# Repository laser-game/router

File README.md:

# Router
Devices for route wireless communication between the control computer and laser game devices.

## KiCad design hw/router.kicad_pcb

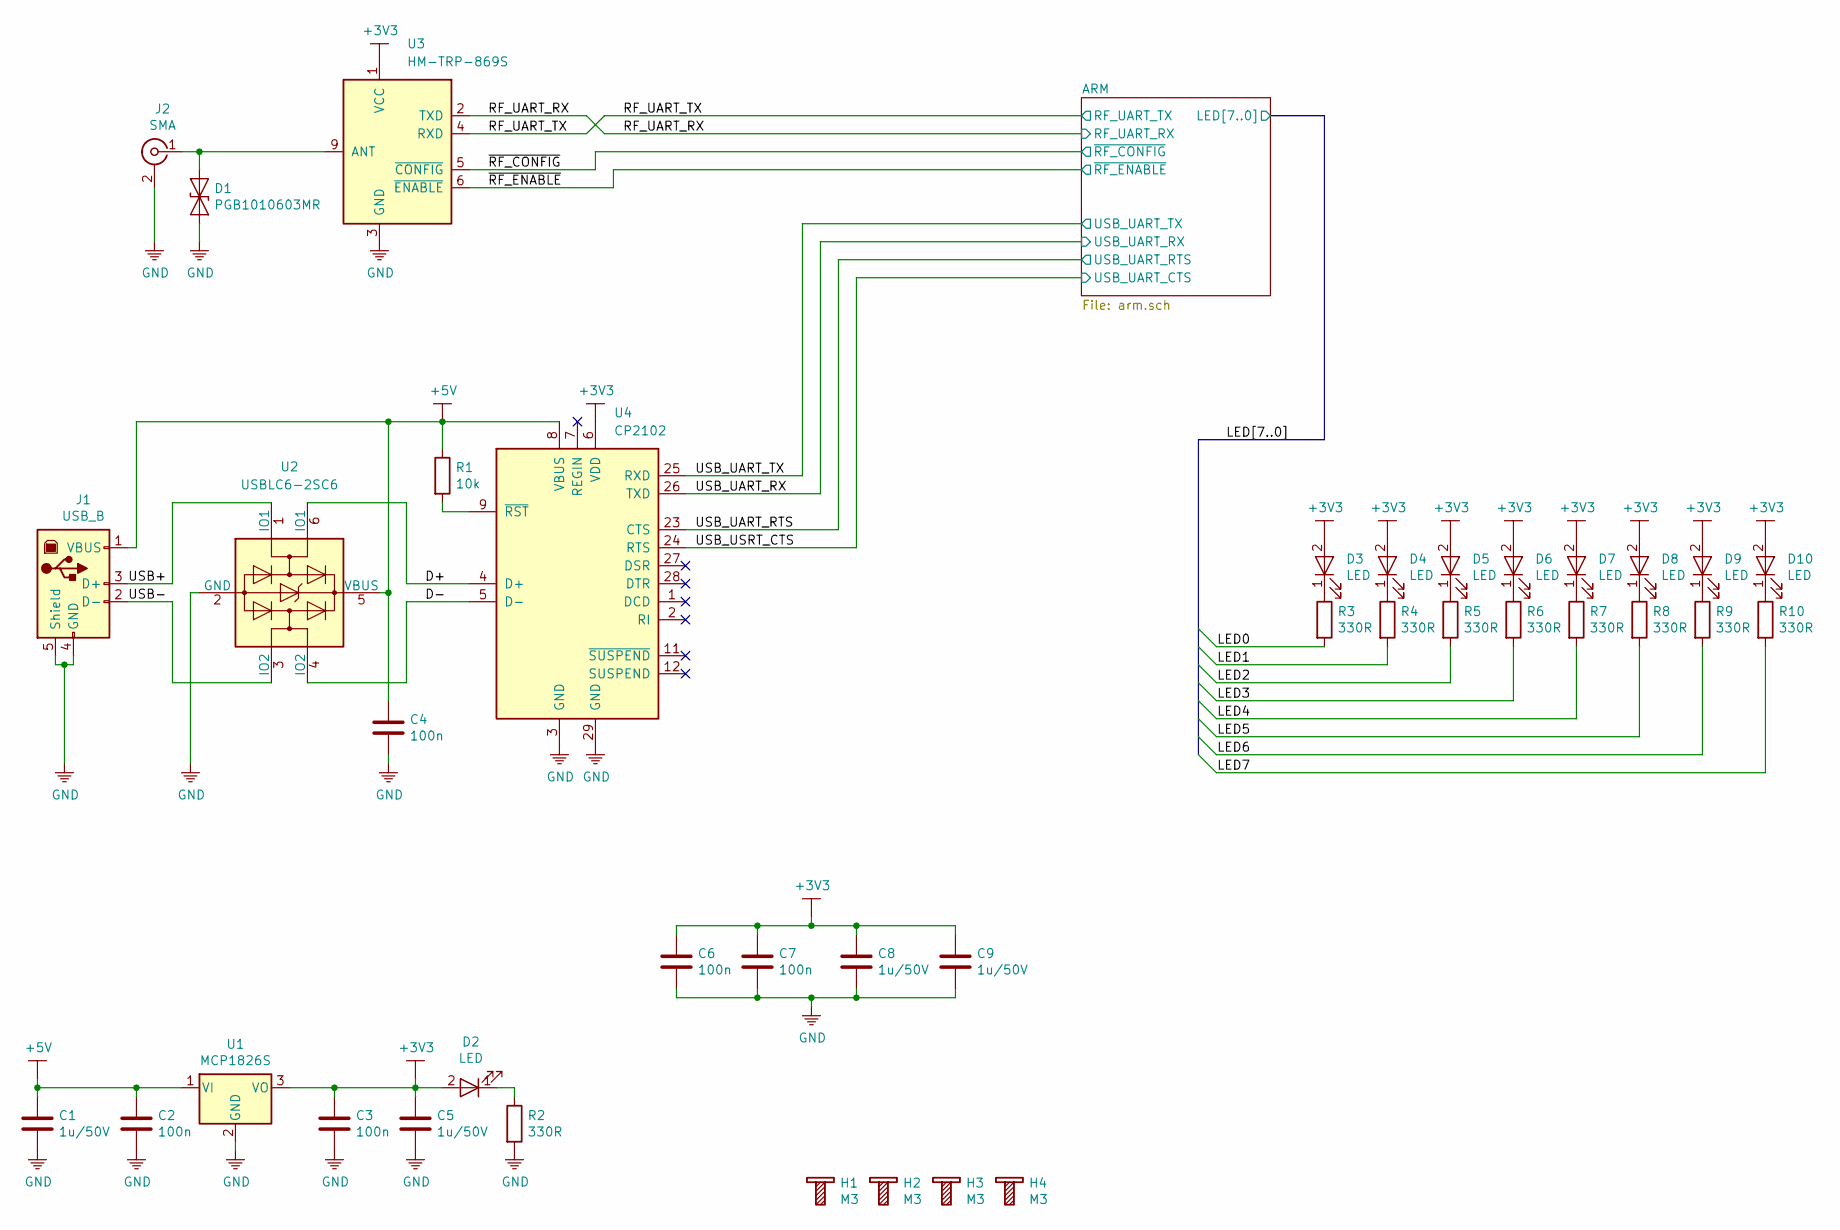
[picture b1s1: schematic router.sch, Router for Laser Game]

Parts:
C1, C5, C8, C9: 1u/50V; C_0805_2012Metric
C2, C3, C4, C6, C7: 100n; C_0805_2012Metric
D1: PGB1010603MR; D_0603_1608Metric
D2, D3, D4, D5, D6, D7, D8, D9, D10: LED; LED_0805_2012Metric
H1, H2, H3, H4: M3; Bolt_M3
J1: USB_B; USB_B_TE_5787834_Vertical
J2: SMA; SMA_Jack_Vertical
R1: 10k; R_0805_2012Metric
R2, R3, R4, R5, R6, R7, R8, R9, R10: 330R; R_0805_2012Metric
U1: MCP1826S; SOT-223-3_TabPin2
U2: USBLC6-2SC6; SOT-23-6
U3: HM-TRP-869S; HM-TRP-SMD
U4: CP2102; QFN-28-1EP_5x5mm_P0.5mm_EP3.35x3.35mm

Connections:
+3V3: C3.1, C5.1, C6.1, C7.1, C8.1, C9.1, D2.2 (A), D3.2 (A), D4.2 (A), D5.2 (A), D6.2 (A), D7.2 (A), D8.2 (A), D9.2 (A), D10.2 (A), U1.3 (VO), U3.1 (VCC), U4.6 (VDD); also elsewhere on the board
+5V: C1.1, C2.1, C4.1, J1.1 (VBUS), R1.1, U1.1 (VI), U2.5 (VBUS), U4.8 (VBUS)
/D+: U2.6 (IO1), U4.4 (D+)
/D-: U2.4 (IO2), U4.5 (D-)
/LED0: R3.2; also elsewhere on the board
/LED1: R4.2; also elsewhere on the board
/LED2: R5.2; also elsewhere on the board
/LED3: R6.2; also elsewhere on the board
/LED4: R7.2; also elsewhere on the board
/LED5: R8.2; also elsewhere on the board
/LED6: R9.2; also elsewhere on the board
/LED7: R10.2; also elsewhere on the board
/RF_UART_RX: U3.2 (TXD); also elsewhere on the board
/RF_UART_TX: U3.4 (RXD); also elsewhere on the board
/USB+: J1.3 (D+), U2.1 (IO1)
/USB-: J1.2 (D-), U2.3 (IO2)
/USB_UART_RTS: U4.23 (CTS); also elsewhere on the board
/USB_UART_RX: U4.26 (TXD); also elsewhere on the board
/USB_UART_TX: U4.25 (RXD); also elsewhere on the board
/USB_USRT_CTS: U4.24 (RTS); also elsewhere on the board
/~RF_CONFIG: U3.5 (~CONFIG); also elsewhere on the board
/~RF_ENABLE: U3.6 (~ENABLE); also elsewhere on the board
GND: C1.2, C2.2, C3.2, C4.2, C5.2, C6.2, C7.2, C8.2, C9.2, D1.2 (A2), J1.4 (GND), J1.5 (Shield), J2.2 (Ext), R2.2, U1.2 (GND), U2.2 (GND), U3.3 (GND), U3.8 (GND), U4.3 (GND), U4.29 (GND); also elsewhere on the board
unnamed: D1.1 (A1), J2.1 (In), U3.9 (ANT)
unnamed: D2.1 (K), R2.1
unnamed: D3.1 (K), R3.1
unnamed: D4.1 (K), R4.1
unnamed: D5.1 (K), R5.1
unnamed: D6.1 (K), R6.1
unnamed: D7.1 (K), R7.1
unnamed: D8.1 (K), R8.1
unnamed: D9.1 (K), R9.1
unnamed: D10.1 (K), R10.1
unnamed: R1.2, U4.9 (~RST)

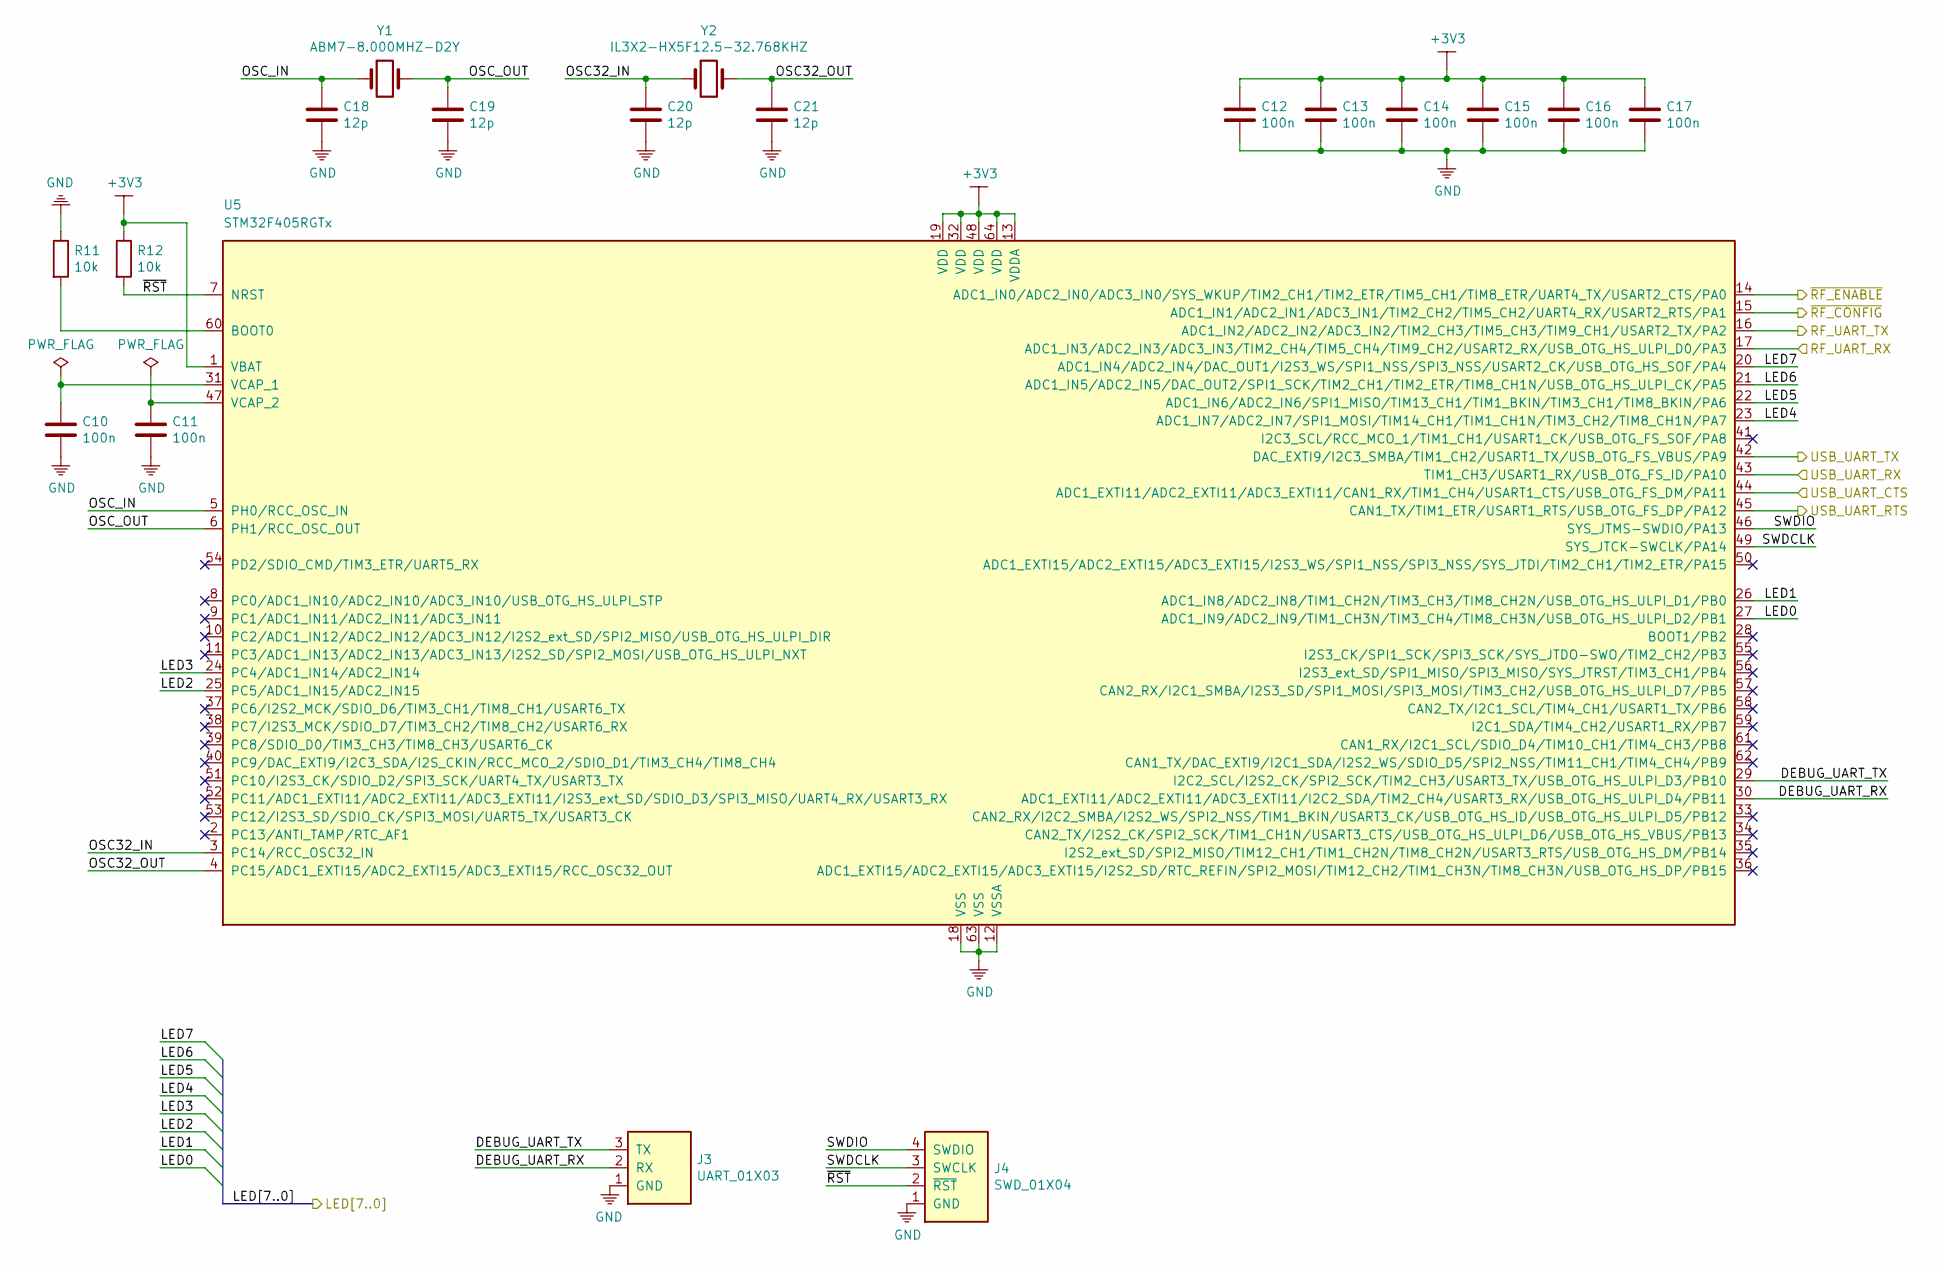
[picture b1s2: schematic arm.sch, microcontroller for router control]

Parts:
C10, C11, C12, C13, C14, C15, C16, C17: 100n; C_0805_2012Metric
C18, C19, C20, C21: 12p; C_0805_2012Metric
J3: UART_01X03; PinHeader_1x03_P2.54mm_Vertical
J4: SWD_01X04; PinHeader_1x04_P2.54mm_Vertical
R11, R12: 10k; R_0805_2012Metric
U5: STM32F405RGTx; TQFP-64_10x10mm_P0.5mm
Y1: ABM7-8.000MHZ-D2Y; Crystal_SMD_2012-2Pin_2.0x1.2mm_HandSoldering
Y2: IL3X2-HX5F12.5-32.768KHZ; Crystal_SMD_2012-2Pin_2.0x1.2mm_HandSoldering

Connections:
+3V3: C12.1, C13.1, C14.1, C15.1, C16.1, C17.1, R12.1, U5.1 (VBAT), U5.13 (VDDA), U5.19 (VDD), U5.32 (VDD), U5.48 (VDD), U5.64 (VDD); also elsewhere on the board
/ARM/DEBUG_UART_RX: J3.2 (RX), U5.30 (ADC1_EXTI11/ADC2_EXTI11/ADC3_EXTI11/I2C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)
/ARM/DEBUG_UART_TX: J3.3 (TX), U5.29 (I2C2_SCL/I2S2_CK/SPI2_SCK/TIM2_CH3/USAR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)
/ARM/OSC32_IN: C20.1, U5.3 (PC14/RCC_OSC32_IN), Y2.1
/ARM/OSC32_OUT: C21.1, U5.4 (PC15/ADC1_EXTI15/ADC2_EXTI15/ADC3_EXTI1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), Y2.2
/ARM/OSC_IN: C18.1, U5.5 (PH0/RCC_OSC_IN), Y1.1
/ARM/OSC_OUT: C19.1, U5.6 (PH1/RCC_OSC_OUT), Y1.2
/ARM/SWDCLK: J4.3 (SWCLK), U5.49 (SYS_JTCK-SWCLK/PA14)
/ARM/SWDIO: J4.4 (SWDIO), U5.46 (SYS_JTMS-SWDIO/PA13)
/ARM/~RST: J4.2 (~RST), R12.2, U5.7 (NRST)
/LED0: U5.27 (ADC1_IN9/ADC2_IN9/TIM1_CH3N/TIM3_CH4/TI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); also elsewhere on the board
/LED1: U5.26 (ADC1_IN8/ADC2_IN8/TIM1_CH2N/TIM3_CH3/TI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); also elsewhere on the board
/LED2: U5.25 (PC5/ADC1_IN15/ADC2_IN15); also elsewhere on the board
/LED3: U5.24 (PC4/ADC1_IN14/ADC2_IN14); also elsewhere on the board
/LED4: U5.23 (ADC1_IN7/ADC2_IN7/SPI1_MOSI/TIM14_CH1/T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); also elsewhere on the board
/LED5: U5.22 (ADC1_IN6/ADC2_IN6/SPI1_MISO/TIM13_CH1/T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); also elsewhere on the board
/LED6: U5.21 (ADC1_IN5/ADC2_IN5/DAC_OUT2/SPI1_SCK/TIM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); also elsewhere on the board
/LED7: U5.20 (ADC1_IN4/ADC2_IN4/DAC_OUT1/I2S3_WS/SPI1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); also elsewhere on the board
/RF_UART_RX: U5.17 (ADC1_IN3/ADC2_IN3/ADC3_IN3/TIM2_CH4/TIM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); also elsewhere on the board
/RF_UART_TX: U5.16 (ADC1_IN2/ADC2_IN2/ADC3_IN2/TIM2_CH3/TIM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); also elsewhere on the board
/USB_UART_RTS: U5.45 (CAN1_TX/TIM1_ETR/USART1_RTS/USB_OTG_FS_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); also elsewhere on the board
/USB_UART_RX: U5.43 (TIM1_CH3/USART1_RX/USB_OTG_FS_ID/PA10); also elsewhere on the board
/USB_UART_TX: U5.42 (DAC_EXTI9/I2C3_SMBA/TIM1_CH2/USART1_TX/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); also elsewhere on the board
/USB_USRT_CTS: U5.44 (ADC1_EXTI11/ADC2_EXTI11/ADC3_EXTI11/CAN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); also elsewhere on the board
/~RF_CONFIG: U5.15 (ADC1_IN1/ADC2_IN1/ADC3_IN1/TIM2_CH2/TIM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); also elsewhere on the board
/~RF_ENABLE: U5.14 (ADC1_IN0/ADC2_IN0/ADC3_IN0/SYS_WKUP/TIM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); also elsewhere on the board
GND: C10.2, C11.2, C12.2, C13.2, C14.2, C15.2, C16.2, C17.2, C18.2, C19.2, C20.2, C21.2, J3.1 (GND), J4.1 (GND), R11.1, U5.12 (VSSA), U5.18 (VSS), U5.63 (VSS); also elsewhere on the board
unnamed: C10.1, U5.31 (VCAP_1)
unnamed: C11.1, U5.47 (VCAP_2)
unnamed: R11.2, U5.60 (BOOT0)

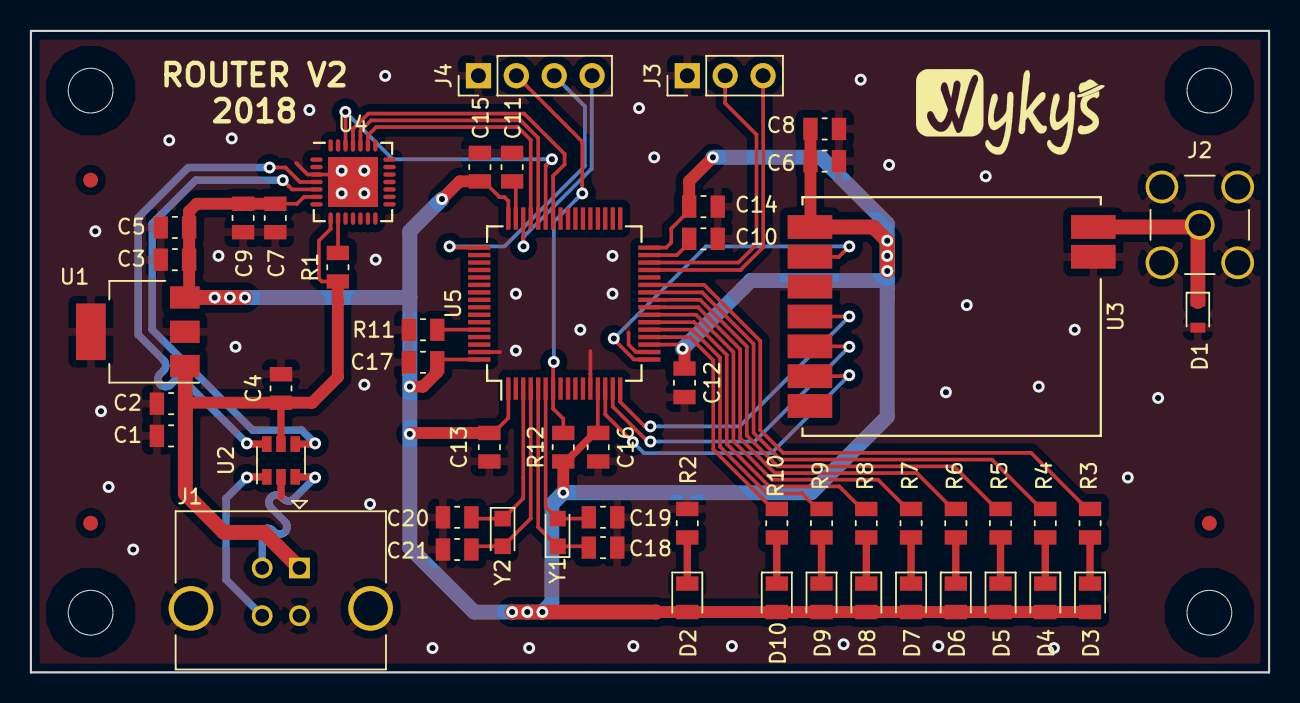
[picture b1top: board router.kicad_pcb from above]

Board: 2 copper layers, 83.0 x 43.0 mm, 58 parts (0 on the bottom side), 46 nets.

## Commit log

2018-03-30 added license
2018-03-30 updated gitignore and readme
2018-03-30 created schematic
2018-04-10 updated gitignore added pdf files
2018-04-10 changed mcu from STM32F401CEUx to STM32F405RGTx and split schematic to more sheets
2018-04-13 updated schematic
2018-04-14 created pcb
2018-04-15 added meanders
2018-04-20 added fiducials
2018-04-20 updated USB footprint
2018-05-02 added boom file and schematic for fabracation
2018-05-06 added placement file
2018-05-08 renamed placement file

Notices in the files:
README.md:
License: CC BY-NC-ND 4.0
